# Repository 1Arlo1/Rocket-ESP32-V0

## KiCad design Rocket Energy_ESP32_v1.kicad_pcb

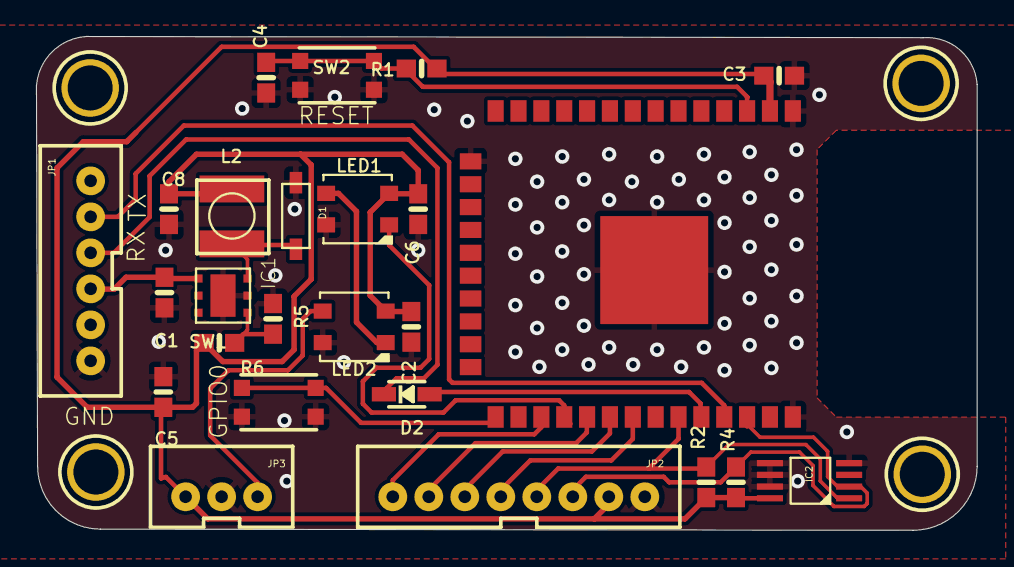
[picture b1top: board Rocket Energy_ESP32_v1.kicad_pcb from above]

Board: 2 copper layers, 52.3 x 27.4 mm, 29 parts (0 on the bottom side), 19 nets.

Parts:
C1: 4.7uF; 0603-NO
C2, C3, C4, C5, C6: 1uF; 0603-NO
C8: 22uf; 0603-NO
D1: BAT54ZFILM; SOD-123
D2: 1n4148; SOD-323
IC1: ST1S03; DFQN6D
IC2: MCP9808; MSOP8
JP1: B6B-PH-K-S(LF)(SN); JST6
JP2: B8B-PH-K-S(LF)(SN); JST8
JP3: B3B-PH-K-S(LF)(SN); JST-3-PTH-VERT
L2: 3.3uh; MICROBUILDER_INDUCTOR_5X5MM_NR5040_NOTHERMALS
LED1, LED2: SK6812MINI; MICROBUILDER_LED3535
R1: 10K; 0603-NO
R2, R4: 4.7k; 0603-NO
R5: 15k; 0603-NO
R6: 47k; 0603-NO
SW1, SW2: KMR2; BTN_KMR2_4.6X2.8
U$8, U$17, U$25, U$27: MOUNTINGHOLE2.5; MOUNTINGHOLE_2.5_PLATED
X2: ESP32-WROOM-32; WROOM32_SKINNY

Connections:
3.3V: C2.1, C3.1, C5.1, C6.1, C8.1, IC2.P$8, JP2.7, JP3.1, L2.P$2, LED1.2, LED2.2, R1.2, R2.2, R4.2, R6.1, X2.2
GND: C1.2, C2.2, C3.2, C4.2, C5.2, C6.2, C8.2, D1.A, IC1.2, IC1.GND, IC2.P$4, IC2.P$5, IC2.P$6, IC2.P$7, JP1.1, JP2.8, JP3.2, LED1.4, LED2.4, R5.2, SW1.A, SW1.A', SW2.A, SW2.A', X2.1, X2.15, X2.38, X2.P$1
GPIO0: SW1.B, SW1.B', X2.25
IO16: JP2.1, X2.27
LED: LED1.1, X2.28
MISO: JP2.4, X2.31
MOSI: JP2.3, X2.30
unnamed: JP3.3, LED2.3
unnamed: LED1.3, LED2.1
unnamed: IC1.1, R5.1, R6.2
unnamed: D1.C, IC1.3, L2.P$1
RESET: C4.1, R1.1, SW2.B, SW2.B', X2.3
RXD0: D2.A, X2.34
RXD_5V: D2.C, JP1.4
SCK: JP2.2, X2.29
SCL: IC2.P$2, JP2.6, R4.1, X2.36
SDA: IC2.P$1, JP2.5, R2.1, X2.33
TXD0: JP1.5, X2.35
VBUS: C1.1, IC1.4, IC1.5, JP1.3
